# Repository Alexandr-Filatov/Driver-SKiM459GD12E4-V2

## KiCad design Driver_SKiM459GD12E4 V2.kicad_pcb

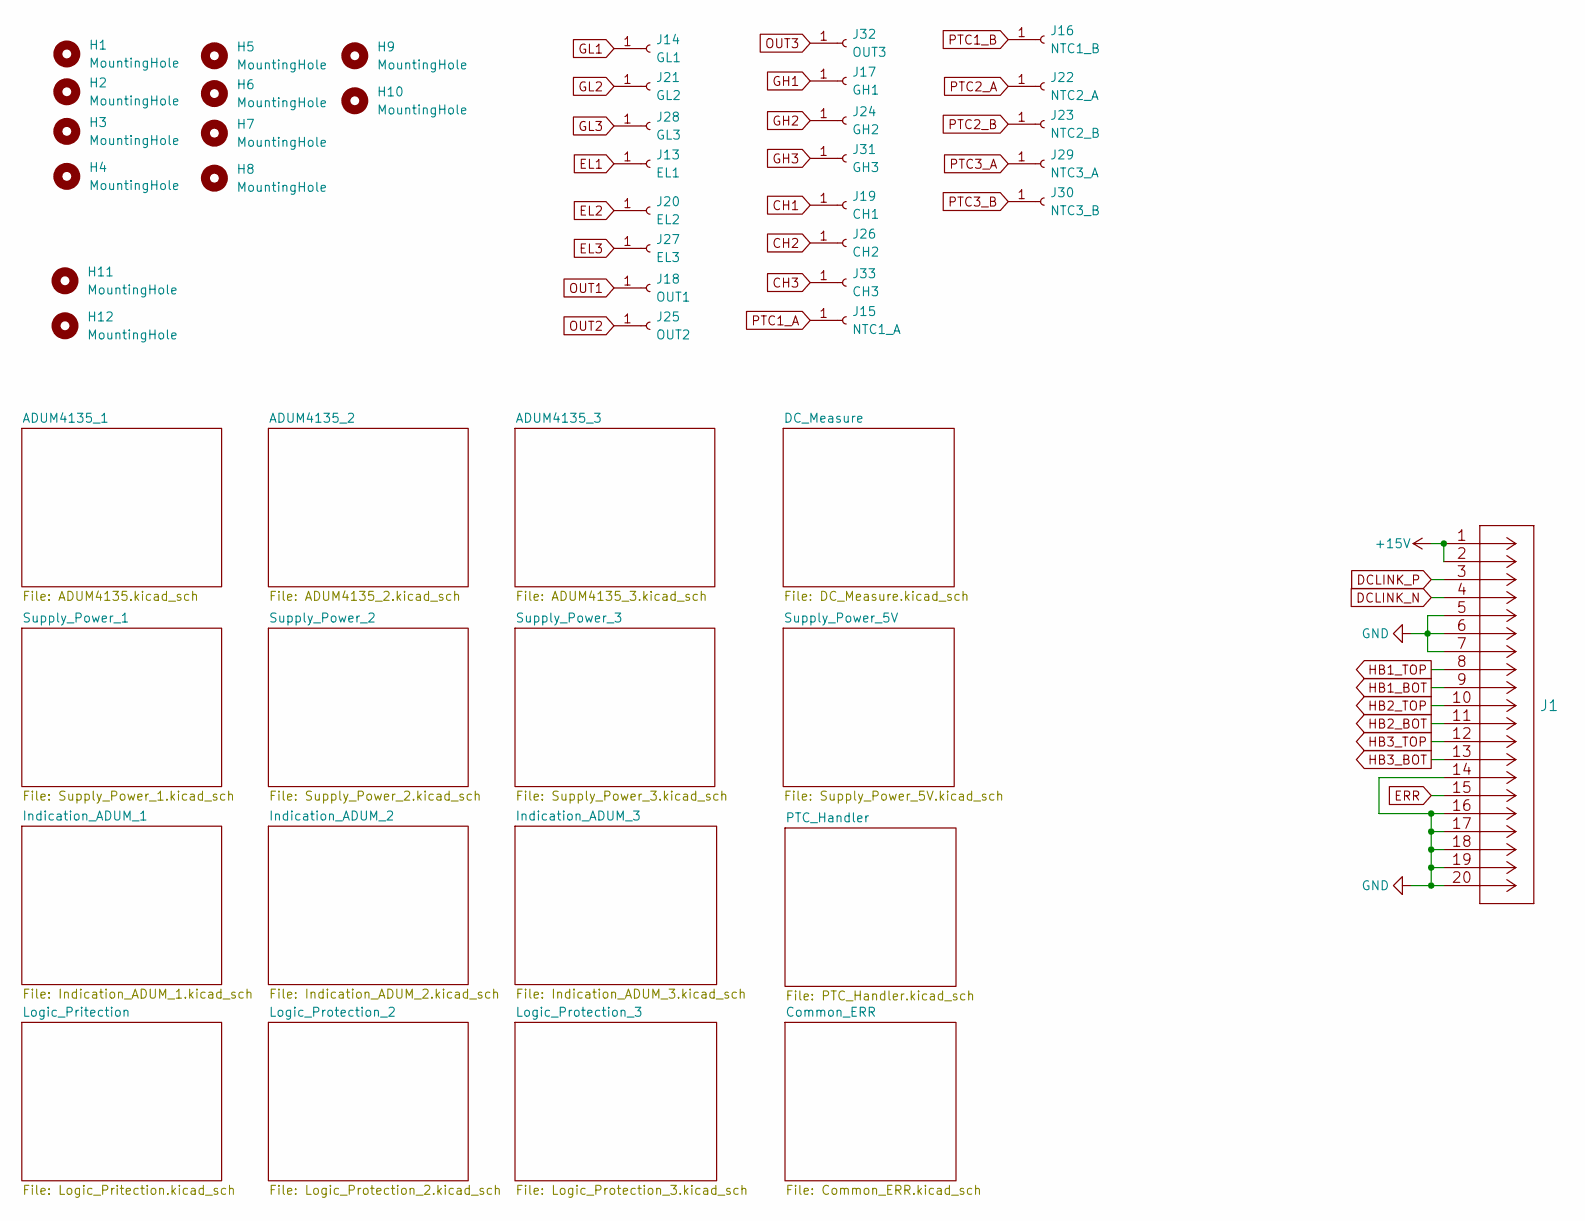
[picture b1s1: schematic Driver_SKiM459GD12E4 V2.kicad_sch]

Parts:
H1, H2, H3, H4, H5, H6, H7, H8, H9, H10: MountingHole; M3
H11, H12: MountingHole; M4
J1: 2-338069-0
J13: EL1; SKiM459GD12E4 V2_SMD_Pin
J14: GL1; SKiM459GD12E4 V2_SMD_Pin
J15: NTC1_A; SKiM459GD12E4 V2_SMD_Pin
J16: NTC1_B; SKiM459GD12E4 V2_SMD_Pin
J17: GH1; SKiM459GD12E4 V2_SMD_Pin
J18: OUT1; SKiM459GD12E4 V2_SMD_Pin
J19: CH1; SKiM459GD12E4 V2_SMD_Pin
J20: EL2; SKiM459GD12E4 V2_SMD_Pin
J21: GL2; SKiM459GD12E4 V2_SMD_Pin
J22: NTC2_A; SKiM459GD12E4 V2_SMD_Pin
J23: NTC2_B; SKiM459GD12E4 V2_SMD_Pin
J24: GH2; SKiM459GD12E4 V2_SMD_Pin
J25: OUT2; SKiM459GD12E4 V2_SMD_Pin
J26: CH2; SKiM459GD12E4 V2_SMD_Pin
J27: EL3; SKiM459GD12E4 V2_SMD_Pin
J28: GL3; SKiM459GD12E4 V2_SMD_Pin
J29: NTC3_A; SKiM459GD12E4 V2_SMD_Pin
J30: NTC3_B; SKiM459GD12E4 V2_SMD_Pin
J31: GH3; SKiM459GD12E4 V2_SMD_Pin
J32: OUT3; SKiM459GD12E4 V2_SMD_Pin
J33: CH3; SKiM459GD12E4 V2_SMD_Pin

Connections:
+15V: J1.1, J1.2; also elsewhere on the board
+15V_L2: J22.1; also elsewhere on the board
CH1: J19.1; also elsewhere on the board
CH2: J26.1; also elsewhere on the board
CH3: J33.1; also elsewhere on the board
DCLINK_N: J1.4; also elsewhere on the board
DCLINK_P: J1.3; also elsewhere on the board
EL1: J13.1; also elsewhere on the board
EL2: J20.1; also elsewhere on the board
EL3: J27.1; also elsewhere on the board
ERR: J1.15; also elsewhere on the board
GH1: J17.1; also elsewhere on the board
GH2: J24.1; also elsewhere on the board
GH3: J31.1; also elsewhere on the board
GL1: J14.1; also elsewhere on the board
GL2: J21.1; also elsewhere on the board
GL3: J28.1; also elsewhere on the board
GND: J1.5, J1.6, J1.7, J1.14, J1.16, J1.17, J1.18, J1.19, J1.20; also elsewhere on the board
HB1_BOT: J1.9; also elsewhere on the board
HB1_TOP: J1.8; also elsewhere on the board
HB2_BOT: J1.11; also elsewhere on the board
HB2_TOP: J1.10; also elsewhere on the board
HB3_BOT: J1.13; also elsewhere on the board
HB3_TOP: J1.12; also elsewhere on the board
OUT1: J18.1; also elsewhere on the board
OUT2: J25.1; also elsewhere on the board
OUT3: J32.1; also elsewhere on the board
PTC1_A: J15.1
PTC1_B: J16.1
PTC2_B: J23.1; also elsewhere on the board
PTC3_A: J29.1
PTC3_B: J30.1

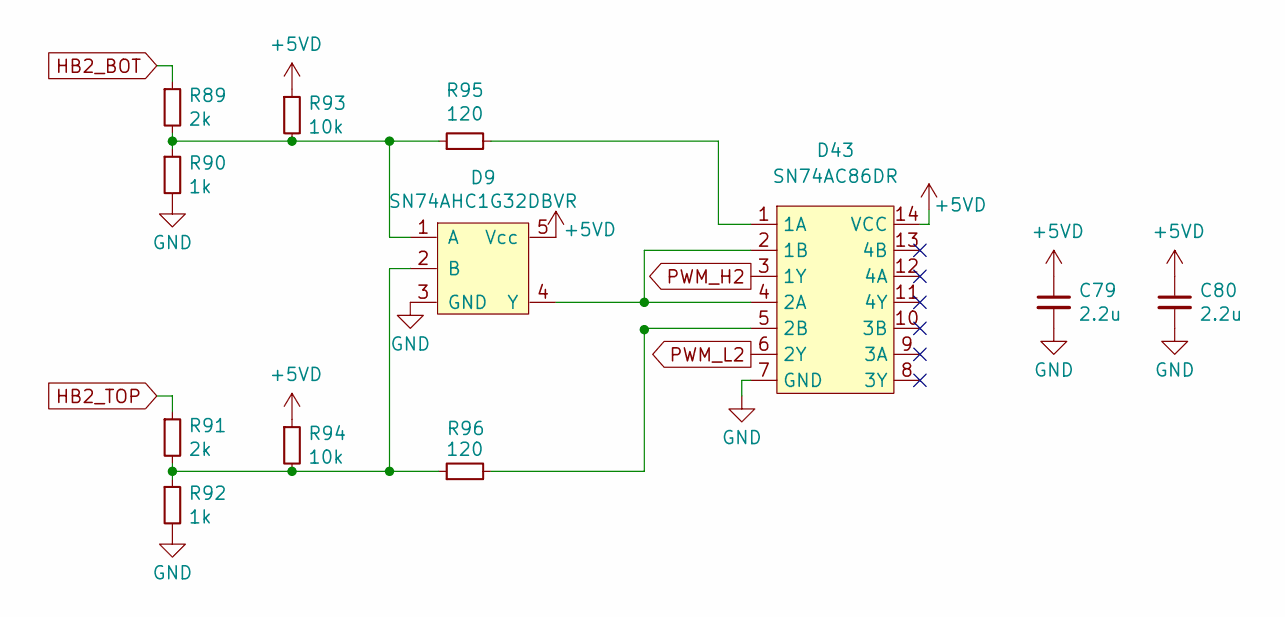
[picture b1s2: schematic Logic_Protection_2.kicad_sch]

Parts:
C79, C80: 2.2u; C_0805_2012Metric_Pad1.18x1.45mm_HandSolder
D9: SN74AHC1G32DBVR; SOT-23-5_HandSoldering
D43: SN74AC86DR; SOIC-14_3.9x8.7mm_P1.27mm
R89, R91: 2k; R_0805_2012Metric_Pad1.20x1.40mm_HandSolder
R90, R92: 1k; R_0805_2012Metric_Pad1.20x1.40mm_HandSolder
R93, R94: 10k; R_0805_2012Metric_Pad1.20x1.40mm_HandSolder
R95, R96: 120; R_0805_2012Metric_Pad1.20x1.40mm_HandSolder

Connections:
+5VD: C79.1, C80.1, D9.5 (Vcc), D43.14 (VCC), R93.1, R94.1; also elsewhere on the board
GND: C79.2, C80.2, D9.3 (GND), D43.7 (GND), R90.2, R92.2; also elsewhere on the board
HB2_BOT: R89.1; also elsewhere on the board
HB2_TOP: R91.1; also elsewhere on the board
unnamed: D9.1 (A), R89.2, R90.1, R93.2, R95.1
unnamed: D9.2 (B), R91.2, R92.1, R94.2, R96.1
unnamed: D43.1 (1A), R95.2
unnamed: D9.4 (Y), D43.2 (1B), D43.4 (2A)
unnamed: D43.5 (2B), R96.2
PWM_H2: D43.3 (1Y); also elsewhere on the board
PWM_L2: D43.6 (2Y); also elsewhere on the board

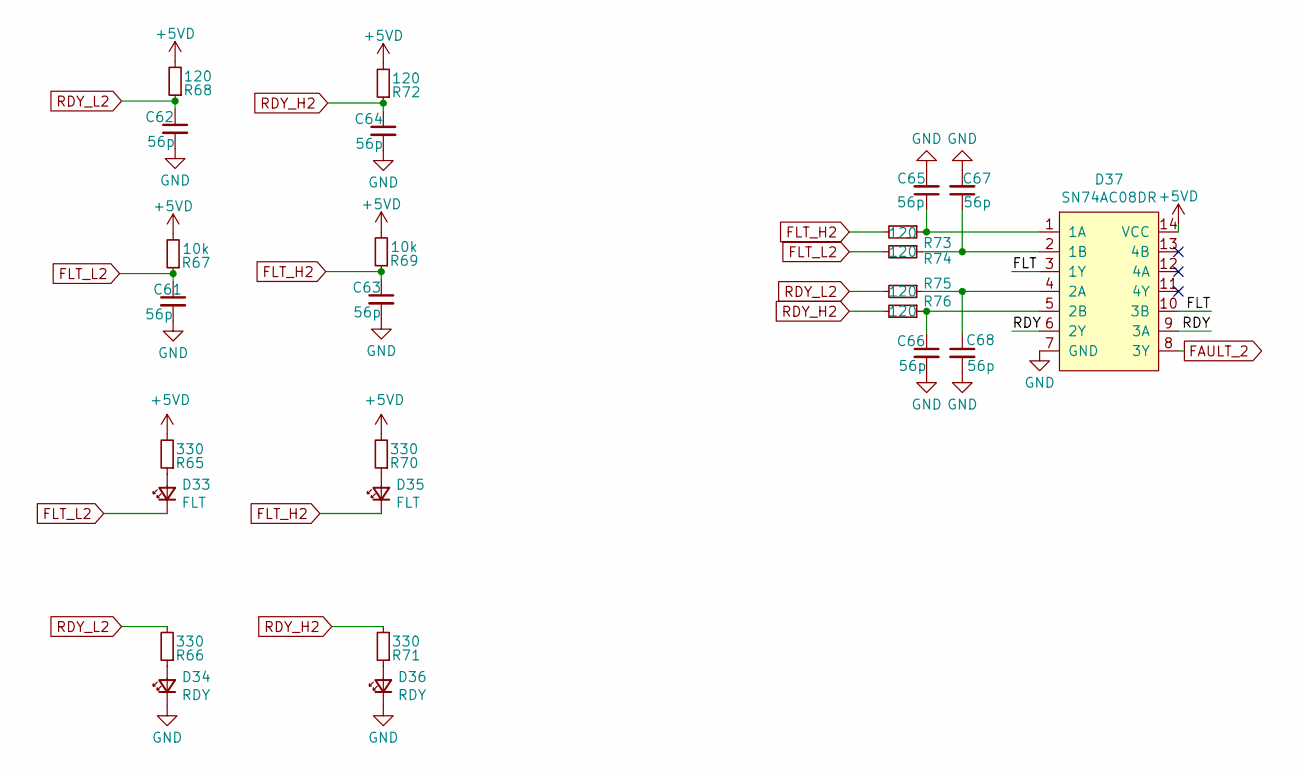
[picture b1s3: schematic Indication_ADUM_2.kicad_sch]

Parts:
C61, C62, C63, C64, C65, C66, C67, C68: 56p; C_0805_2012Metric_Pad1.18x1.45mm_HandSolder
D33, D35: FLT; LED_0805_2012Metric_Pad1.15x1.40mm_HandSolder
D34, D36: RDY; LED_0805_2012Metric_Pad1.15x1.40mm_HandSolder
D37: SN74AC08DR; SOIC-14_3.9x8.7mm_P1.27mm
R65, R66, R70, R71: 330; R_0805_2012Metric_Pad1.20x1.40mm_HandSolder
R67, R69: 10k; R_0805_2012Metric_Pad1.20x1.40mm_HandSolder
R68, R72, R73, R74, R75, R76: 120; R_0805_2012Metric_Pad1.20x1.40mm_HandSolder

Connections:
+5VD: D37.14 (VCC), R65.2, R67.2, R68.2, R69.2, R70.2, R72.2; also elsewhere on the board
/Indication_ADUM_2/FLT: D37.3 (1Y), D37.10 (3B)
/Indication_ADUM_2/RDY: D37.6 (2Y), D37.9 (3A)
FAULT_2: D37.8 (3Y); also elsewhere on the board
FLT_H2: C63.1, D35.1 (K), R69.1, R73.2; also elsewhere on the board
FLT_L2: C61.1, D33.1 (K), R67.1, R74.2; also elsewhere on the board
GND: C61.2, C62.2, C63.2, C64.2, C65.2, C66.2, C67.2, C68.2, D34.1 (K), D36.1 (K), D37.7 (GND); also elsewhere on the board
unnamed: D33.2 (A), R65.1
unnamed: D34.2 (A), R66.1
unnamed: D35.2 (A), R70.1
unnamed: D36.2 (A), R71.1
unnamed: C65.1, D37.1 (1A), R73.1
unnamed: C67.1, D37.2 (1B), R74.1
unnamed: C68.1, D37.4 (2A), R75.1
unnamed: C66.1, D37.5 (2B), R76.1
RDY_H2: C64.1, R71.2, R72.1, R76.2; also elsewhere on the board
RDY_L2: C62.1, R66.2, R68.1, R75.2; also elsewhere on the board

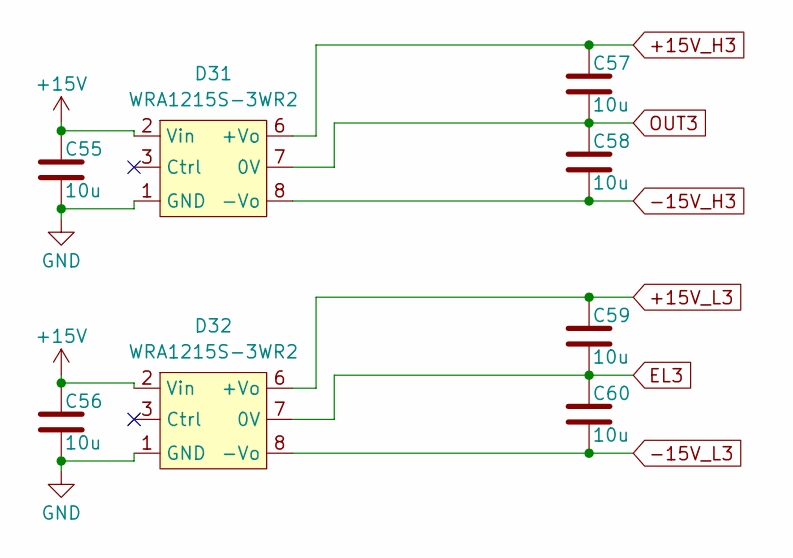
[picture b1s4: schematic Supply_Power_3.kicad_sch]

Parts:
C55, C56, C57, C58, C59, C60: 10u; C_1210_3225Metric_Pad1.33x2.70mm_HandSolder
D31, D32: WRA1215S-3WR2

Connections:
+15V: C55.1, C56.1, D31.2 (Vin), D32.2 (Vin); also elsewhere on the board
+15V_H3: C57.1, D31.6 (+Vo); also elsewhere on the board
+15V_L3: C59.1, D32.6 (+Vo); also elsewhere on the board
-15V_H3: C58.2, D31.8 (-Vo); also elsewhere on the board
-15V_L3: C60.2, D32.8 (-Vo); also elsewhere on the board
EL3: C59.2, C60.1, D32.7 (0V); also elsewhere on the board
GND: C55.2, C56.2, D31.1 (GND), D32.1 (GND); also elsewhere on the board
OUT3: C57.2, C58.1, D31.7 (0V); also elsewhere on the board

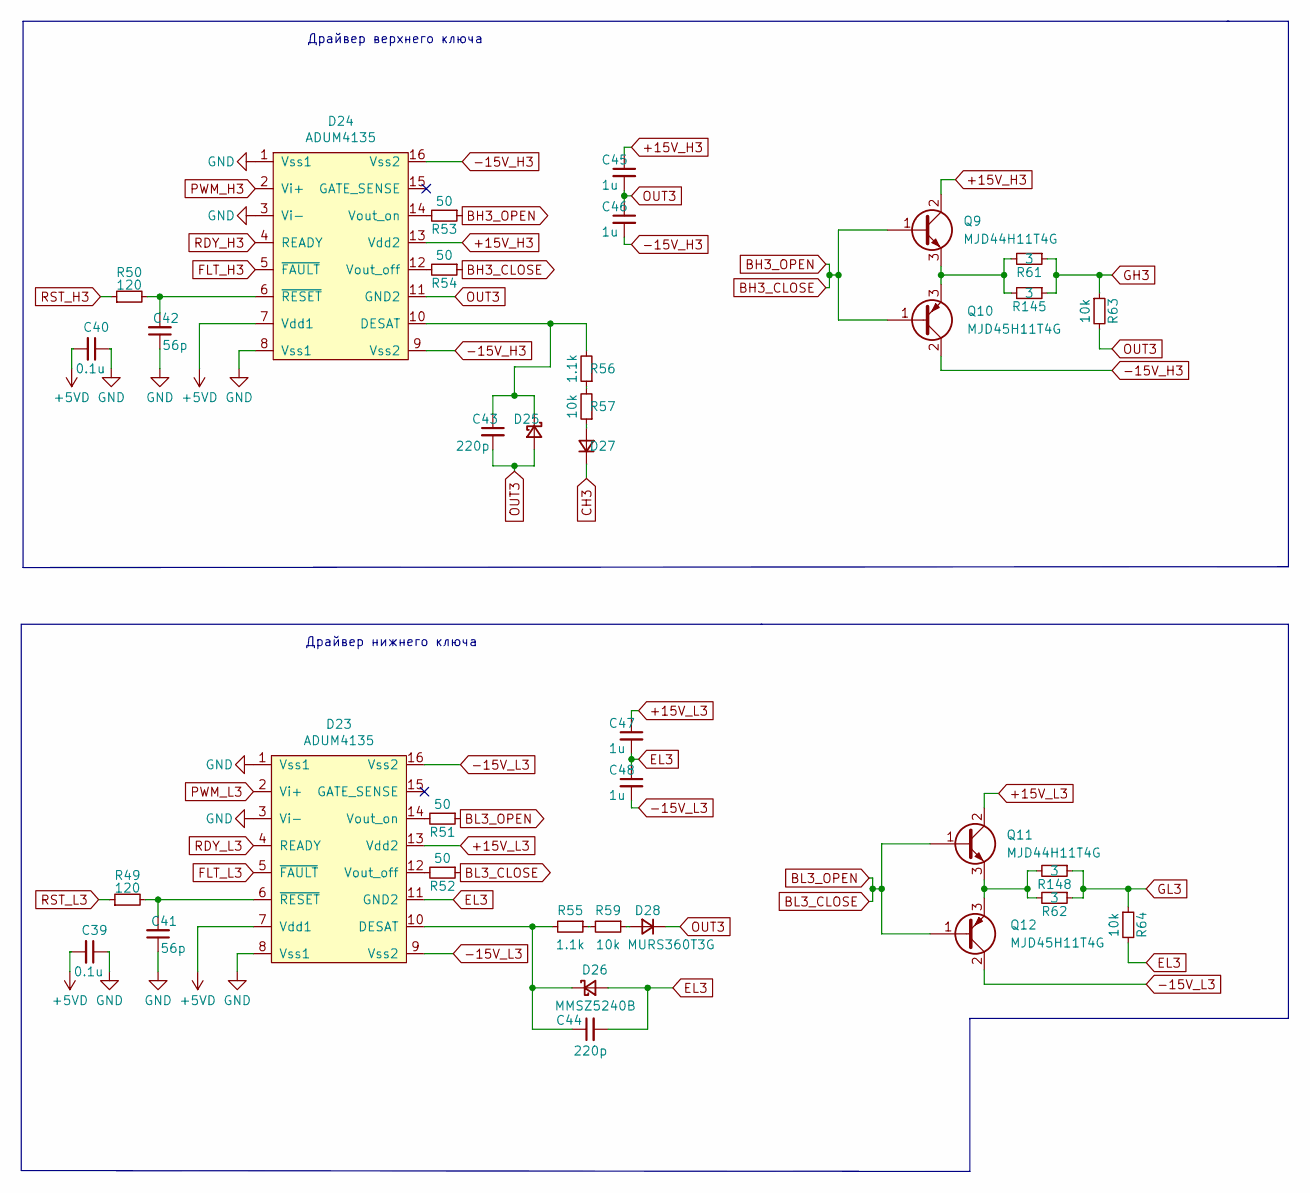
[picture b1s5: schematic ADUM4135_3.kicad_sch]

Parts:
C39, C40: 0.1u; C_0805_2012Metric_Pad1.18x1.45mm_HandSolder
C41, C42: 56p; C_0805_2012Metric_Pad1.18x1.45mm_HandSolder
C43, C44: 220p; C_0805_2012Metric_Pad1.18x1.45mm_HandSolder
C45, C46, C47, C48: 1u; C_0805_2012Metric_Pad1.18x1.45mm_HandSolder
D23, D24: ADUM4135; SOIC-16W_7.5x10.3mm_P1.27mm
D25, D26: MMSZ5240B; D_SOD-123
D27, D28: MURS360T3G; D_SMC
Q9, Q11: MJD44H11T4G; TO-252-2
Q10, Q12: MJD45H11T4G; TO-252-2
R49, R50: 120; R_0805_2012Metric_Pad1.20x1.40mm_HandSolder
R51, R52, R53, R54: 50; R_1210_3225Metric_Pad1.30x2.65mm_HandSolder
R55, R56: 1.1k; R_0805_2012Metric_Pad1.20x1.40mm_HandSolder
R57, R59: 10k; R_1206_3216Metric_Pad1.30x1.75mm_HandSolder
R61, R62, R145, R148: 3; R_2512_6332Metric_Pad1.40x3.35mm_HandSolder
R63, R64: 10k; R_1210_3225Metric_Pad1.30x2.65mm_HandSolder

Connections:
+5VD: C39.2, C40.2, D23.7 (Vdd1), D24.7 (Vdd1); also elsewhere on the board
+15V_H3: C45.1, D24.13 (Vdd2), Q9.2 (C), Q9.4 (C); also elsewhere on the board
+15V_L3: C47.1, D23.13 (Vdd2), Q11.2 (C), Q11.4 (C); also elsewhere on the board
-15V_H3: C46.2, D24.9 (Vss2), D24.16 (Vss2), Q10.2 (C); also elsewhere on the board
-15V_L3: C48.2, D23.9 (Vss2), D23.16 (Vss2), Q12.2 (C); also elsewhere on the board
BH3_CLOSE: Q9.1 (B), Q10.1 (B), R53.1, R54.1
BL3_CLOSE: Q11.1 (B), Q12.1 (B), R51.1, R52.1
CH3: D27.1 (K); also elsewhere on the board
EL3: C44.2, C47.2, C48.1, D23.11 (GND2), D26.2 (A), R64.2; also elsewhere on the board
FLT_H3: D24.5 (~FAULT); also elsewhere on the board
FLT_L3: D23.5 (~FAULT); also elsewhere on the board
GH3: R61.1, R63.1, R145.1; also elsewhere on the board
GL3: R62.1, R64.1, R148.1; also elsewhere on the board
GND: C39.1, C40.1, C41.1, C42.1, D23.1 (Vss1), D23.3 (Vi-), D23.8 (Vss1), D24.1 (Vss1), D24.3 (Vi-), D24.8 (Vss1); also elsewhere on the board
unnamed: C44.1, D23.10 (DESAT), D26.1 (K), R55.2
unnamed: D23.12 (Vout_off), R52.2
unnamed: D23.14 (Vout_on), R51.2
unnamed: C41.2, D23.6 (~RESET), R49.2
unnamed: C43.1, D24.10 (DESAT), D25.1 (K), R56.2
unnamed: D24.12 (Vout_off), R54.2
unnamed: D24.14 (Vout_on), R53.2
unnamed: C42.2, D24.6 (~RESET), R50.2
unnamed: D27.2 (A), R57.1
unnamed: D28.2 (A), R59.1
unnamed: Q9.3 (E), Q10.3 (E), R61.2, R145.2
unnamed: Q11.3 (E), Q12.3 (E), R62.2, R148.2
unnamed: R55.1, R59.2
unnamed: R56.1, R57.2
OUT3: C43.2, C45.2, C46.1, D24.11 (GND2), D25.2 (A), D28.1 (K), R63.2; also elsewhere on the board
PWM_H3: D24.2 (Vi+); also elsewhere on the board
PWM_L3: D23.2 (Vi+); also elsewhere on the board
RDY_H3: D24.4 (READY); also elsewhere on the board
RDY_L3: D23.4 (READY); also elsewhere on the board
RST_H1: R49.1, R50.1; also elsewhere on the board

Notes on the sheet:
Драйвер нижнего ключа
Драйвер верхнего ключа

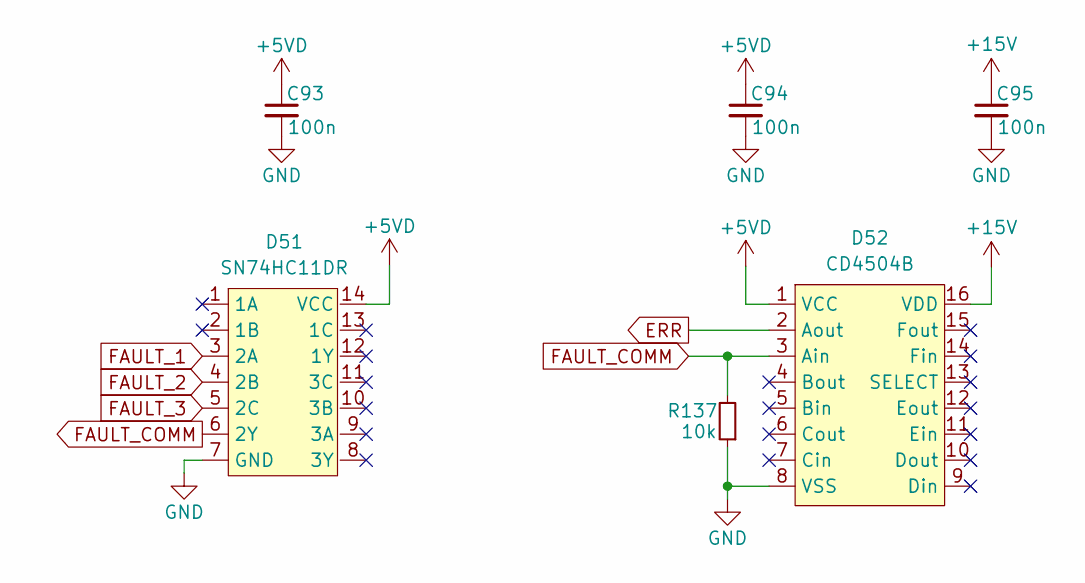
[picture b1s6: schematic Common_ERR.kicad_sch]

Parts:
C93, C94, C95: 100n; C_0805_2012Metric_Pad1.18x1.45mm_HandSolder
D51: SN74HC11DR; SOIC-14_3.9x8.7mm_P1.27mm
D52: CD4504B; SOP-16_3.9x9.9mm_P1.27mm
R137: 10k; R_0805_2012Metric_Pad1.20x1.40mm_HandSolder

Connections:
+5VD: C93.1, C94.1, D51.14 (VCC), D52.1 (VCC); also elsewhere on the board
+15V: C95.1, D52.16 (VDD); also elsewhere on the board
ERR: D52.2 (Aout); also elsewhere on the board
FAULT_1: D51.3 (2A); also elsewhere on the board
FAULT_2: D51.4 (2B); also elsewhere on the board
FAULT_3: D51.5 (2C); also elsewhere on the board
FAULT_COMM: D51.6 (2Y), D52.3 (Ain), R137.2
GND: C93.2, C94.2, C95.2, D51.7 (GND), D52.8 (VSS), R137.1; also elsewhere on the board

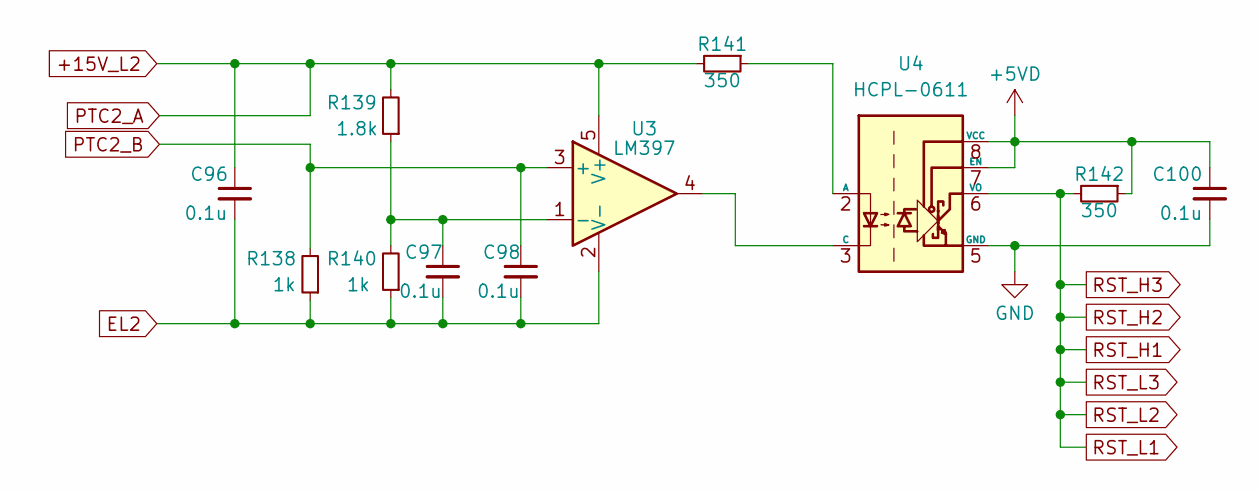
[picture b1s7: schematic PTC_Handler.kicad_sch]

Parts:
C96, C97, C98, C100: 0.1u; C_0805_2012Metric_Pad1.18x1.45mm_HandSolder
R138, R140: 1k; R_0805_2012Metric_Pad1.20x1.40mm_HandSolder
R139: 1.8k; R_0805_2012Metric_Pad1.20x1.40mm_HandSolder
R141, R142: 350; R_0805_2012Metric_Pad1.20x1.40mm_HandSolder
U3: LM397; SOT-23-5
U4: HCPL-0611; SOIC-8_3.9x4.9mm_P1.27mm

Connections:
+5VD: C100.1, R142.1, U4.7 (EN), U4.8 (VCC); also elsewhere on the board
+15V_L2: C96.1, R139.2, R141.2, U3.5 (V+); also elsewhere on the board
EL2: C96.2, C97.2, C98.2, R138.1, R140.1, U3.2 (V-); also elsewhere on the board
GND: C100.2, U4.5 (GND); also elsewhere on the board
unnamed: C97.1, R139.1, R140.2, U3.1 (-)
unnamed: R141.1, U4.2 (A)
unnamed: U3.4, U4.3 (C)
PTC2_B: C98.1, R138.2, U3.3 (+); also elsewhere on the board
RST_H1: R142.2, U4.6 (VO); also elsewhere on the board

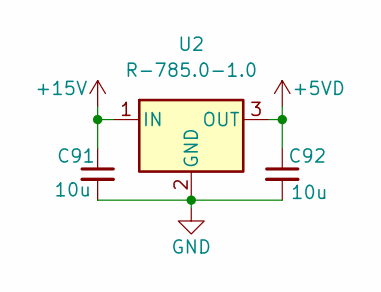
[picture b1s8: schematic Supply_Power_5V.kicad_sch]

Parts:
C91, C92: 10u; C_1210_3225Metric_Pad1.33x2.70mm_HandSolder
U2: R-785.0-1.0; Converter_DCDC_RECOM_R-78E-0.5_THT

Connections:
+5VD: C92.1, U2.3 (OUT); also elsewhere on the board
+15V: C91.1, U2.1 (IN); also elsewhere on the board
GND: C91.2, C92.2, U2.2 (GND); also elsewhere on the board

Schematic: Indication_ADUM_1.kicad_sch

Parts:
C11, C12, C13, C14, C15, C16, C17, C18: 56p; C_0805_2012Metric_Pad1.18x1.45mm_HandSolder
D10, D12: FLT; LED_0805_2012Metric_Pad1.15x1.40mm_HandSolder
D11, D13: RDY; LED_0805_2012Metric_Pad1.15x1.40mm_HandSolder
D14: SN74AC08DR; SOIC-14_3.9x8.7mm_P1.27mm
R17, R18, R22, R23: 330; R_0805_2012Metric_Pad1.20x1.40mm_HandSolder
R19, R21: 10k; R_0805_2012Metric_Pad1.20x1.40mm_HandSolder
R20, R24, R25, R26, R27, R28: 120; R_0805_2012Metric_Pad1.20x1.40mm_HandSolder

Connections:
+5VD: D14.14 (VCC), R17.2, R19.2, R20.2, R21.2, R22.2, R24.2; also elsewhere on the board
/Indication_ADUM_1/FLT: D14.3 (1Y), D14.10 (3B)
/Indication_ADUM_1/RDY: D14.6 (2Y), D14.9 (3A)
FAULT_1: D14.8 (3Y); also elsewhere on the board
FLT_H1: C13.1, D12.1 (K), R21.1, R25.2; also elsewhere on the board
FLT_L1: C11.1, D10.1 (K), R19.1, R26.2; also elsewhere on the board
GND: C11.2, C12.2, C13.2, C14.2, C15.2, C16.2, C17.2, C18.2, D11.1 (K), D13.1 (K), D14.7 (GND); also elsewhere on the board
unnamed: D10.2 (A), R17.1
unnamed: D11.2 (A), R18.1
unnamed: D12.2 (A), R22.1
unnamed: D13.2 (A), R23.1
unnamed: C15.1, D14.1 (1A), R25.1
unnamed: C17.1, D14.2 (1B), R26.1
unnamed: C18.1, D14.4 (2A), R27.1
unnamed: C16.1, D14.5 (2B), R28.1
RDY_H1: C14.1, R23.2, R24.1, R28.2; also elsewhere on the board
RDY_L1: C12.1, R18.2, R20.1, R27.2; also elsewhere on the board

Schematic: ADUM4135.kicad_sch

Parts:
C1, C4: 0.1u; C_0805_2012Metric_Pad1.18x1.45mm_HandSolder
C2, C5: 56p; C_0805_2012Metric_Pad1.18x1.45mm_HandSolder
C3, C6: 220p; C_0805_2012Metric_Pad1.18x1.45mm_HandSolder
C21, C22, C27, C28: 1u; C_0805_2012Metric_Pad1.18x1.45mm_HandSolder
D1, D4: ADUM4135; SOIC-16W_7.5x10.3mm_P1.27mm
D2, D6: MURS360T3G; D_SMC
D3, D5: MMSZ5240B; D_SOD-123
Q1, Q3: MJD44H11T4G; TO-252-2
Q2, Q4: MJD45H11T4G; TO-252-2
R1, R7: 120; R_0805_2012Metric_Pad1.20x1.40mm_HandSolder
R2, R3, R8, R9: 50; R_1210_3225Metric_Pad1.30x2.65mm_HandSolder
R4, R12: 10k; R_1206_3216Metric_Pad1.30x1.75mm_HandSolder
R5, R10: 1.1k; R_0805_2012Metric_Pad1.20x1.40mm_HandSolder
R29, R30, R143, R146: 3; R_2512_6332Metric_Pad1.40x3.35mm_HandSolder
R31, R32: 10k; R_1210_3225Metric_Pad1.30x2.65mm_HandSolder

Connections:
+5VD: C1.2, C4.2, D1.7 (Vdd1), D4.7 (Vdd1); also elsewhere on the board
+15V_H1: C21.1, D1.13 (Vdd2), Q1.2 (C), Q1.4 (C); also elsewhere on the board
+15V_L1: C27.1, D4.13 (Vdd2), Q3.2 (C), Q3.4 (C); also elsewhere on the board
-15V_H1: C22.2, D1.9 (Vss2), D1.16 (Vss2), Q2.2 (C); also elsewhere on the board
-15V_L1: C28.2, D4.9 (Vss2), D4.16 (Vss2), Q4.2 (C); also elsewhere on the board
BH1_CLOSE: Q1.1 (B), Q2.1 (B), R2.1, R3.1
BL1_CLOSE: Q3.1 (B), Q4.1 (B), R8.1, R9.1
CH1: D2.1 (K); also elsewhere on the board
EL1: C6.2, C27.2, C28.1, D4.11 (GND2), D5.2 (A), R32.2; also elsewhere on the board
FLT_H1: D1.5 (~FAULT); also elsewhere on the board
FLT_L1: D4.5 (~FAULT); also elsewhere on the board
GH1: R29.1, R31.1, R143.1; also elsewhere on the board
GL1: R30.1, R32.1, R146.1; also elsewhere on the board
GND: C1.1, C2.1, C4.1, C5.1, D1.1 (Vss1), D1.3 (Vi-), D1.8 (Vss1), D4.1 (Vss1), D4.3 (Vi-), D4.8 (Vss1); also elsewhere on the board
unnamed: C3.1, D1.10 (DESAT), D3.1 (K), R5.2
unnamed: D1.12 (Vout_off), R3.2
unnamed: D1.14 (Vout_on), R2.2
unnamed: C2.2, D1.6 (~RESET), R1.2
unnamed: D2.2 (A), R4.1
unnamed: C6.1, D4.10 (DESAT), D5.1 (K), R10.2
unnamed: D4.12 (Vout_off), R9.2
unnamed: D4.14 (Vout_on), R8.2
unnamed: C5.2, D4.6 (~RESET), R7.2
unnamed: D6.2 (A), R12.1
unnamed: Q1.3 (E), Q2.3 (E), R29.2, R143.2
unnamed: Q3.3 (E), Q4.3 (E), R30.2, R146.2
unnamed: R4.2, R5.1
unnamed: R10.1, R12.2
OUT1: C3.2, C21.2, C22.1, D1.11 (GND2), D3.2 (A), D6.1 (K), R31.2; also elsewhere on the board
PWM_H1: D1.2 (Vi+); also elsewhere on the board
PWM_L1: D4.2 (Vi+); also elsewhere on the board
RDY_H1: D1.4 (READY); also elsewhere on the board
RDY_L1: D4.4 (READY); also elsewhere on the board
RST_H1: R1.1, R7.1; also elsewhere on the board

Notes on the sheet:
Драйвер верхнего ключа
Драйвер нижнего ключа

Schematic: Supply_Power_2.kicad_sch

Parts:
C49, C50, C51, C52, C53, C54: 10u; C_1210_3225Metric_Pad1.33x2.70mm_HandSolder
D29, D30: WRA1215S-3WR2

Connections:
+15V: C49.1, C50.1, D29.2 (Vin), D30.2 (Vin); also elsewhere on the board
+15V_H2: C53.1, D30.6 (+Vo); also elsewhere on the board
+15V_L2: C51.1, D29.6 (+Vo); also elsewhere on the board
-15V_H2: C54.2, D30.8 (-Vo); also elsewhere on the board
-15V_L2: C52.2, D29.8 (-Vo); also elsewhere on the board
EL2: C51.2, C52.1, D29.7 (0V); also elsewhere on the board
GND: C49.2, C50.2, D29.1 (GND), D30.1 (GND); also elsewhere on the board
OUT2: C53.2, C54.1, D30.7 (0V); also elsewhere on the board

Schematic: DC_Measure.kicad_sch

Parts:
C85: 0.1u; C_1206_3216Metric_Pad1.33x1.80mm_HandSolder
C86, C87, C88, C89, C90: 1n; C_0805_2012Metric_Pad1.18x1.45mm_HandSolder
C99: 0.1u; C_0805_2012Metric_Pad1.18x1.45mm_HandSolder
D49, D50: 1SMB5929BT3G; D_SMB
R97, R98, R99, R100, R101, R102, R103, R104, R105, R106, R107, R108, R109, R110, R111, R112, R115, R116, R117, R120: 910k; R_0805_2012Metric_Pad1.20x1.40mm_HandSolder
R113: 3k; R_0805_2012Metric_Pad1.20x1.40mm_HandSolder
R114: 3.3k; R_0805_2012Metric_Pad1.20x1.40mm_HandSolder
R118, R119: 27k; R_0805_2012Metric_Pad1.20x1.40mm_HandSolder
R121, R122: 1k; R_0805_2012Metric_Pad1.20x1.40mm_HandSolder
R123, R124: 10; R_0805_2012Metric_Pad1.20x1.40mm_HandSolder
U1: LM2904; SO-8_3.9x4.9mm_P1.27mm

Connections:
+15V: C99.1, R114.2, U1.8 (V+); also elsewhere on the board
CH3: R97.1; also elsewhere on the board
DCLINK_N: C89.1, D49.1 (K), R123.2, U1.7; also elsewhere on the board
DCLINK_P: C90.1, D50.1 (K), R124.2, U1.1; also elsewhere on the board
EL3: R104.1; also elsewhere on the board
GND: C86.1, C87.1, C88.2, C99.2, D49.2 (A), D50.2 (A), R113.1, U1.4 (V-); also elsewhere on the board
unnamed: C86.2, R113.2, R114.1, R118.2, R119.1
unnamed: R97.2, R98.1
unnamed: R98.2, R99.1
unnamed: R100.1, R105.1
unnamed: R99.2, R100.2
unnamed: R101.1, R106.1
unnamed: R101.2, R102.1
unnamed: R102.2, R103.1
unnamed: R103.2, R104.2
unnamed: R105.2, R107.1
unnamed: R106.2, R108.1
unnamed: R107.2, R109.1
unnamed: R108.2, R110.1
unnamed: R109.2, R111.1
unnamed: R110.2, R112.1
unnamed: R111.2, R115.1
unnamed: R112.2, R116.1
unnamed: R115.2, R117.1
unnamed: R116.2, R120.2
unnamed: R121.2, R123.1
unnamed: R122.2, R124.1
unnamed: C85.1, C87.2, R117.2, R118.1, U1.3 (+)
unnamed: C90.2, R122.1, U1.2 (-)
unnamed: C85.2, C88.1, R119.2, R120.1, U1.5 (+)
unnamed: C89.2, R121.1, U1.6 (-)

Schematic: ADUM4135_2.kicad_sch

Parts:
C29, C30: 0.1u; C_0805_2012Metric_Pad1.18x1.45mm_HandSolder
C31, C32: 56p; C_0805_2012Metric_Pad1.18x1.45mm_HandSolder
C33, C34: 220p; C_0805_2012Metric_Pad1.18x1.45mm_HandSolder
C35, C36, C37, C38: 1u; C_0805_2012Metric_Pad1.18x1.45mm_HandSolder
D17, D18: ADUM4135; SOIC-16W_7.5x10.3mm_P1.27mm
D19, D20: MMSZ5240B; D_SOD-123
D21, D22: MURS360T3G; D_SMC
Q5, Q7: MJD44H11T4G; TO-252-2
Q6, Q8: MJD45H11T4G; TO-252-2
R33, R34: 120; R_0805_2012Metric_Pad1.20x1.40mm_HandSolder
R35, R36, R37, R38: 50; R_1210_3225Metric_Pad1.30x2.65mm_HandSolder
R39, R40: 1.1k; R_0805_2012Metric_Pad1.20x1.40mm_HandSolder
R41, R43: 10k; R_1206_3216Metric_Pad1.30x1.75mm_HandSolder
R45, R46, R144, R147: 3; R_2512_6332Metric_Pad1.40x3.35mm_HandSolder
R47, R48: 10k; R_1210_3225Metric_Pad1.30x2.65mm_HandSolder

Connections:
+5VD: C29.2, C30.2, D17.7 (Vdd1), D18.7 (Vdd1); also elsewhere on the board
+15V_H2: C35.1, D18.13 (Vdd2), Q5.2 (C), Q5.4 (C); also elsewhere on the board
+15V_L2: C37.1, D17.13 (Vdd2), Q7.2 (C), Q7.4 (C); also elsewhere on the board
-15V_H2: C36.2, D18.9 (Vss2), D18.16 (Vss2), Q6.2 (C); also elsewhere on the board
-15V_L2: C38.2, D17.9 (Vss2), D17.16 (Vss2), Q8.2 (C); also elsewhere on the board
BH2_CLOSE: Q5.1 (B), Q6.1 (B), R37.1, R38.1
BL2_CLOSE: Q7.1 (B), Q8.1 (B), R35.1, R36.1
CH2: D21.1 (K); also elsewhere on the board
EL2: C34.2, C37.2, C38.1, D17.11 (GND2), D20.2 (A), R48.2; also elsewhere on the board
FLT_H2: D18.5 (~FAULT); also elsewhere on the board
FLT_L2: D17.5 (~FAULT); also elsewhere on the board
GH2: R45.1, R47.1, R144.1; also elsewhere on the board
GL2: R46.1, R48.1, R147.1; also elsewhere on the board
GND: C29.1, C30.1, C31.1, C32.1, D17.1 (Vss1), D17.3 (Vi-), D17.8 (Vss1), D18.1 (Vss1), D18.3 (Vi-), D18.8 (Vss1); also elsewhere on the board
unnamed: C34.1, D17.10 (DESAT), D20.1 (K), R39.2
unnamed: D17.12 (Vout_off), R36.2
unnamed: D17.14 (Vout_on), R35.2
unnamed: C31.2, D17.6 (~RESET), R33.2
unnamed: C33.1, D18.10 (DESAT), D19.1 (K), R40.2
unnamed: D18.12 (Vout_off), R38.2
unnamed: D18.14 (Vout_on), R37.2
unnamed: C32.2, D18.6 (~RESET), R34.2
unnamed: D21.2 (A), R41.1
unnamed: D22.2 (A), R43.1
unnamed: Q5.3 (E), Q6.3 (E), R45.2, R144.2
unnamed: Q7.3 (E), Q8.3 (E), R46.2, R147.2
unnamed: R39.1, R43.2
unnamed: R40.1, R41.2
OUT2: C33.2, C35.2, C36.1, D18.11 (GND2), D19.2 (A), D22.1 (K), R47.2; also elsewhere on the board
PWM_H2: D18.2 (Vi+); also elsewhere on the board
PWM_L2: D17.2 (Vi+); also elsewhere on the board
RDY_H2: D18.4 (READY); also elsewhere on the board
RDY_L2: D17.4 (READY); also elsewhere on the board
RST_H1: R33.1, R34.1; also elsewhere on the board

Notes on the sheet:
Драйвер нижнего ключа
Драйвер верхнего ключа

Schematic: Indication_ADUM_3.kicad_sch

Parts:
C69, C70, C71, C72, C73, C74, C75, C76: 56p; C_0805_2012Metric_Pad1.18x1.45mm_HandSolder
D38, D40: FLT; LED_0805_2012Metric_Pad1.15x1.40mm_HandSolder
D39, D41: RDY; LED_0805_2012Metric_Pad1.15x1.40mm_HandSolder
D42: SN74AC08DR; SOIC-14_3.9x8.7mm_P1.27mm
R77, R78, R82, R83: 330; R_0805_2012Metric_Pad1.20x1.40mm_HandSolder
R79, R81: 10k; R_0805_2012Metric_Pad1.20x1.40mm_HandSolder
R80, R84, R85, R86, R87, R88: 120; R_0805_2012Metric_Pad1.20x1.40mm_HandSolder

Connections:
+5VD: D42.14 (VCC), R77.2, R79.2, R80.2, R81.2, R82.2, R84.2; also elsewhere on the board
/Indication_ADUM_3/FLT: D42.3 (1Y), D42.10 (3B)
/Indication_ADUM_3/RDY: D42.6 (2Y), D42.9 (3A)
FAULT_3: D42.8 (3Y); also elsewhere on the board
FLT_H3: C71.1, D40.1 (K), R81.1, R85.2; also elsewhere on the board
FLT_L3: C69.1, D38.1 (K), R79.1, R86.2; also elsewhere on the board
GND: C69.2, C70.2, C71.2, C72.2, C73.2, C74.2, C75.2, C76.2, D39.1 (K), D41.1 (K), D42.7 (GND); also elsewhere on the board
unnamed: D38.2 (A), R77.1
unnamed: D39.2 (A), R78.1
unnamed: D40.2 (A), R82.1
unnamed: D41.2 (A), R83.1
unnamed: C73.1, D42.1 (1A), R85.1
unnamed: C75.1, D42.2 (1B), R86.1
unnamed: C76.1, D42.4 (2A), R87.1
unnamed: C74.1, D42.5 (2B), R88.1
RDY_H3: C72.1, R83.2, R84.1, R88.2; also elsewhere on the board
RDY_L3: C70.1, R78.2, R80.1, R87.2; also elsewhere on the board

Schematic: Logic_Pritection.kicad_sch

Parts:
C9, C10: 2.2u; C_0805_2012Metric_Pad1.18x1.45mm_HandSolder
D7: SN74AHC1G32DBVR; SOT-23-5_HandSoldering
D8: SN74AC86DR; SOIC-14_3.9x8.7mm_P1.27mm
R13, R14: 10k; R_0805_2012Metric_Pad1.20x1.40mm_HandSolder
R15, R16: 120; R_0805_2012Metric_Pad1.20x1.40mm_HandSolder
R125, R127: 2k; R_0805_2012Metric_Pad1.20x1.40mm_HandSolder
R126, R128: 1k; R_0805_2012Metric_Pad1.20x1.40mm_HandSolder

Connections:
+5VD: C9.1, C10.1, D7.5 (Vcc), D8.14 (VCC), R13.1, R14.1; also elsewhere on the board
GND: C9.2, C10.2, D7.3 (GND), D8.7 (GND), R126.2, R128.2; also elsewhere on the board
HB1_BOT: R125.1; also elsewhere on the board
HB1_TOP: R127.1; also elsewhere on the board
unnamed: D7.1 (A), R13.2, R15.1, R125.2, R126.1
unnamed: D7.2 (B), R14.2, R16.1, R127.2, R128.1
unnamed: D7.4 (Y), D8.2 (1B), D8.4 (2A)
unnamed: D8.1 (1A), R15.2
unnamed: D8.5 (2B), R16.2
PWM_H1: D8.3 (1Y); also elsewhere on the board
PWM_L1: D8.6 (2Y); also elsewhere on the board

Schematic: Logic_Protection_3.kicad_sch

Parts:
C83, C84: 2.2u; C_0805_2012Metric_Pad1.18x1.45mm_HandSolder
D44: SN74AHC1G32DBVR; SOT-23-5_HandSoldering
D45: SN74AC86DR; SOIC-14_3.9x8.7mm_P1.27mm
R129, R131: 2k; R_0805_2012Metric_Pad1.20x1.40mm_HandSolder
R130, R132: 1k; R_0805_2012Metric_Pad1.20x1.40mm_HandSolder
R133, R134: 10k; R_0805_2012Metric_Pad1.20x1.40mm_HandSolder
R135, R136: 120; R_0805_2012Metric_Pad1.20x1.40mm_HandSolder

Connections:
+5VD: C83.1, C84.1, D44.5 (Vcc), D45.14 (VCC), R133.1, R134.1; also elsewhere on the board
GND: C83.2, C84.2, D44.3 (GND), D45.7 (GND), R130.2, R132.2; also elsewhere on the board
HB3_BOT: R129.1; also elsewhere on the board
HB3_TOP: R131.1; also elsewhere on the board
unnamed: D44.1 (A), R129.2, R130.1, R133.2, R135.1
unnamed: D44.2 (B), R131.2, R132.1, R134.2, R136.1
unnamed: D44.4 (Y), D45.2 (1B), D45.4 (2A)
unnamed: D45.1 (1A), R135.2
unnamed: D45.5 (2B), R136.2
PWM_H3: D45.3 (1Y); also elsewhere on the board
PWM_L3: D45.6 (2Y); also elsewhere on the board

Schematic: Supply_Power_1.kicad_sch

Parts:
C19, C20, C23, C24, C25, C26: 10u; C_1210_3225Metric_Pad1.33x2.70mm_HandSolder
D15, D16: WRA1215S-3WR2

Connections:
+15V: C19.1, C20.1, D15.2 (Vin), D16.2 (Vin); also elsewhere on the board
+15V_H1: C25.1, D16.6 (+Vo); also elsewhere on the board
+15V_L1: C23.1, D15.6 (+Vo); also elsewhere on the board
-15V_H1: C26.2, D16.8 (-Vo); also elsewhere on the board
-15V_L1: C24.2, D15.8 (-Vo); also elsewhere on the board
EL1: C23.2, C24.1, D15.7 (0V); also elsewhere on the board
GND: C19.2, C20.2, D15.1 (GND), D16.1 (GND); also elsewhere on the board
OUT1: C25.2, C26.1, D16.7 (0V); also elsewhere on the board
